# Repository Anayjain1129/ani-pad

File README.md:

# Ani-Pad

### Why did I make it?
As I already made hackpad So i wanna make sure that this submission is not hackpad
This is a easier project for highway. So, i made this project cause I use a 60% keeb which does not have a numpad and I really needed that so i asked alex can i make one and got a yes so here we go

### What was the hardest part about this ?
I had tons of issues with making the Firmware, I was really fucked up on Firmware part but I made through.

Features:

- EC11 Rotary Encoder - For Volume, Brightness etc
- 17x keys
- XIAO rp2040
- Traditional Numpad Layout
- QMK firmware
  
### Schematic

### PCB 

### Case
- Bottom

-Middle plate

- Top

### 3D view of all parts together 
-PCB

-CAD

#Yoututb Link
https://youtube.com/shorts/V-X0GS2zixY?si=X8VkAyLvjKdzDLy9

### BOM
| Name                                                          | Qty | Final Price - INR (USD) | Link                                                                                                                        |
| ------------------------------------------------------------- | --- | ----------------------- | ----------------------------------------------------------------------------------------------------------                  |
| Gateron EF Grayish                                            | 20  | 390 ($4.55)             | [here](https://neomacro.in/products/gateron-ef-grayish)                                                                     |
| Genuine Cherry MX Plate Mount Stabilizers 2U                  | 3   | 400 {$4.67}             | [here](https://stackskb.com/store/genuine-cherry-mx-plate-mount-stabilizers-2u/)                                            |
| KeyKobo Jindo Keycap Set                                      | 1   | 1,700 ($19.84)          | [here](https://neomacro.in/products/key-kobo-jindo-keycap-set?_pos=3&_sid=b1e2b9343&_ss=r&variant=48328446116118)           |
| Diode 1N4148 Through - Hole                                   | 100 | 169 ($1.97)             | [here](https://amzn.in/d/j3eLvoh)                                                                                           |
| EC11 Rotary Encoder                                           | 2   | 178 ($2.08)             | [here](https://amzn.in/d/hVRxzij)                                                                                           |
| M3 x 20mm Bolt                                                | 15  | 149 ($1.73)             | [here](https://amzn.in/d/8GRQWAB)                                                                                           |
| M3 Nuts                                                       | 8   | 100 ($1.16)             | [here](https://amzn.in/d/7UQtsm8)                                                                                           |
| M3 x 5mm Heatset Insert                                       | 25  | 179 ($2.09)             | [here](https://amzn.in/d/ixybuAc)                                                                                           |
| PCB                                                           | 5   | 2,282 ($26.63)          | 
| XIAO 2040                                                     | 1   | 1,340 ($15.64)          | [here](https://www.amazon.in/Microcontroller-Dual-Core-MicroPython-CircuitPython-Interfaces/dp/B09NNVNW7M/ref=sr_1_2_mod_primary_new?sbo=RZvfv%2F%2FHxDF%2BO5021pAnSA%3D%3D&sr=8-2)|
| Top Case                                                      | 1   | Print Legion            |
| Bottom Case                                                   | 1   | Print Legion            |
| Middle Plate                                                  | 1   | Print Legion            |

## Total Pricing 

This Numpad comes out to be 6887 INR ($80.36) When ordering all the parts I'm not including  the 3D parts because I will be getting them from Print Legion.

## Notes :-

I want all the three 3D-printed parts to be printed in black color.
The pricing might slightly vary due to flash sales, and dollar market trends.

## Changes for reboot 
https://drive.google.com/file/d/1S1DNsVMGy2zWwLPmCcZhrC4ZR8giEo4_/view?usp=sharing

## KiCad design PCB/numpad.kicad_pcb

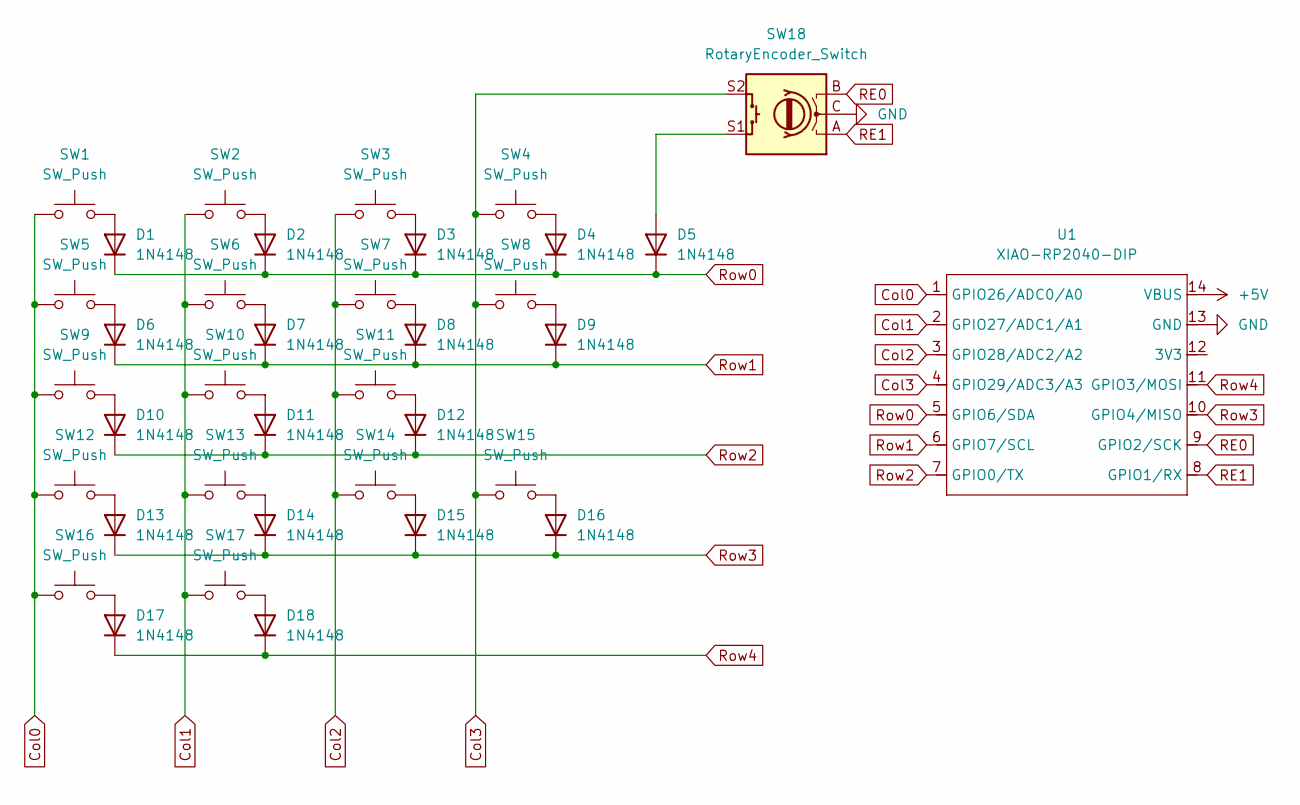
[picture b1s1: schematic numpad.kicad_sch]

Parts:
D1, D2, D3, D4, D5, D6, D7, D8, D9, D10, D11, D12, D13, D14, D15, D16, D17, D18: 1N4148; D_DO-35_SOD27_P7.62mm_Horizontal
SW1, SW2, SW3, SW4, SW5, SW6, SW7, SW9, SW10, SW11, SW12, SW13, SW14, SW17: SW_Push; SW_Cherry_MX_1.00u_PCB
SW8, SW15: SW_Push; SW_Cherry_MX_2.00u_Vertical_PCB
SW16: SW_Push; SW_Cherry_MX_2.00u_PCB
SW18: RotaryEncoder_Switch; RotaryEncoder_Alps_EC11E-Switch_Vertical_H20mm_CircularMoun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
U1: XIAO-RP2040-DIP

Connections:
+5V: U1.14 (VBUS)
Col0: SW1.1, SW5.1, SW9.1, SW12.1, SW16.1, U1.1 (GPIO26/ADC0/A0)
Col1: SW2.1, SW6.1, SW10.1, SW13.1, SW17.1, U1.2 (GPIO27/ADC1/A1)
Col2: SW3.1, SW7.1, SW11.1, SW14.1, U1.3 (GPIO28/ADC2/A2)
Col3: SW4.1, SW8.1, SW15.1, SW18.S2, U1.4 (GPIO29/ADC3/A3)
GND: SW18.C, U1.13 (GND)
unnamed: D1.2 (A), SW1.2
unnamed: D2.2 (A), SW2.2
unnamed: D3.2 (A), SW3.2
unnamed: D4.2 (A), SW4.2
unnamed: D5.2 (A), SW18.S1
unnamed: D6.2 (A), SW5.2
unnamed: D7.2 (A), SW6.2
unnamed: D8.2 (A), SW7.2
unnamed: D9.2 (A), SW8.2
unnamed: D10.2 (A), SW9.2
unnamed: D11.2 (A), SW10.2
unnamed: D12.2 (A), SW11.2
unnamed: D13.2 (A), SW12.2
unnamed: D14.2 (A), SW13.2
unnamed: D15.2 (A), SW14.2
unnamed: D16.2 (A), SW15.2
unnamed: D17.2 (A), SW16.2
unnamed: D18.2 (A), SW17.2
RE0: SW18.B, U1.9 (GPIO2/SCK)
RE1: SW18.A, U1.8 (GPIO1/RX)
Row0: D1.1 (K), D2.1 (K), D3.1 (K), D4.1 (K), D5.1 (K), U1.5 (GPIO6/SDA)
Row1: D6.1 (K), D7.1 (K), D8.1 (K), D9.1 (K), U1.6 (GPIO7/SCL)
Row2: D10.1 (K), D11.1 (K), D12.1 (K), U1.7 (GPIO0/TX)
Row3: D13.1 (K), D14.1 (K), D15.1 (K), D16.1 (K), U1.10 (GPIO4/MISO)
Row4: D17.1 (K), D18.1 (K), U1.11 (GPIO3/MOSI)

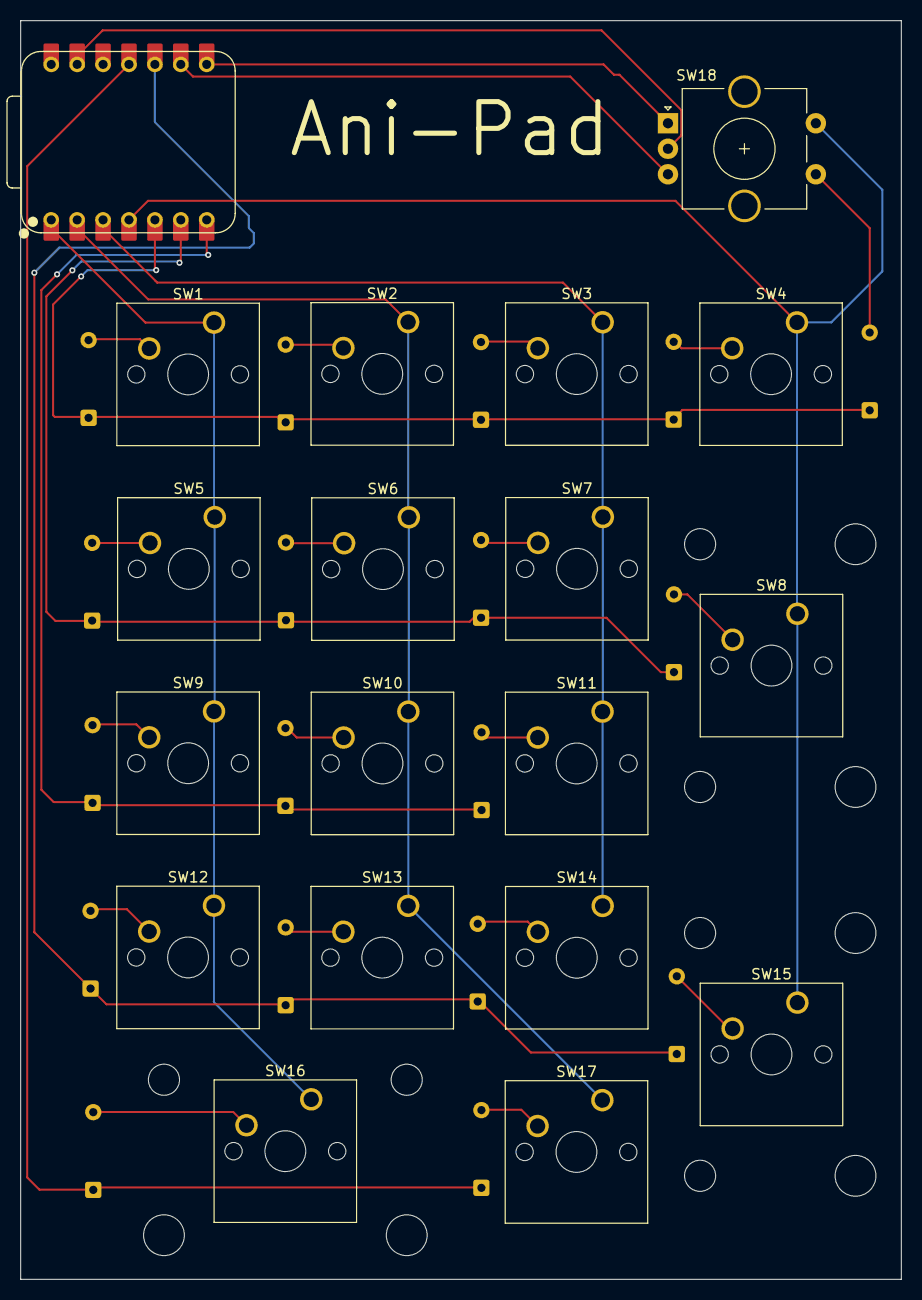
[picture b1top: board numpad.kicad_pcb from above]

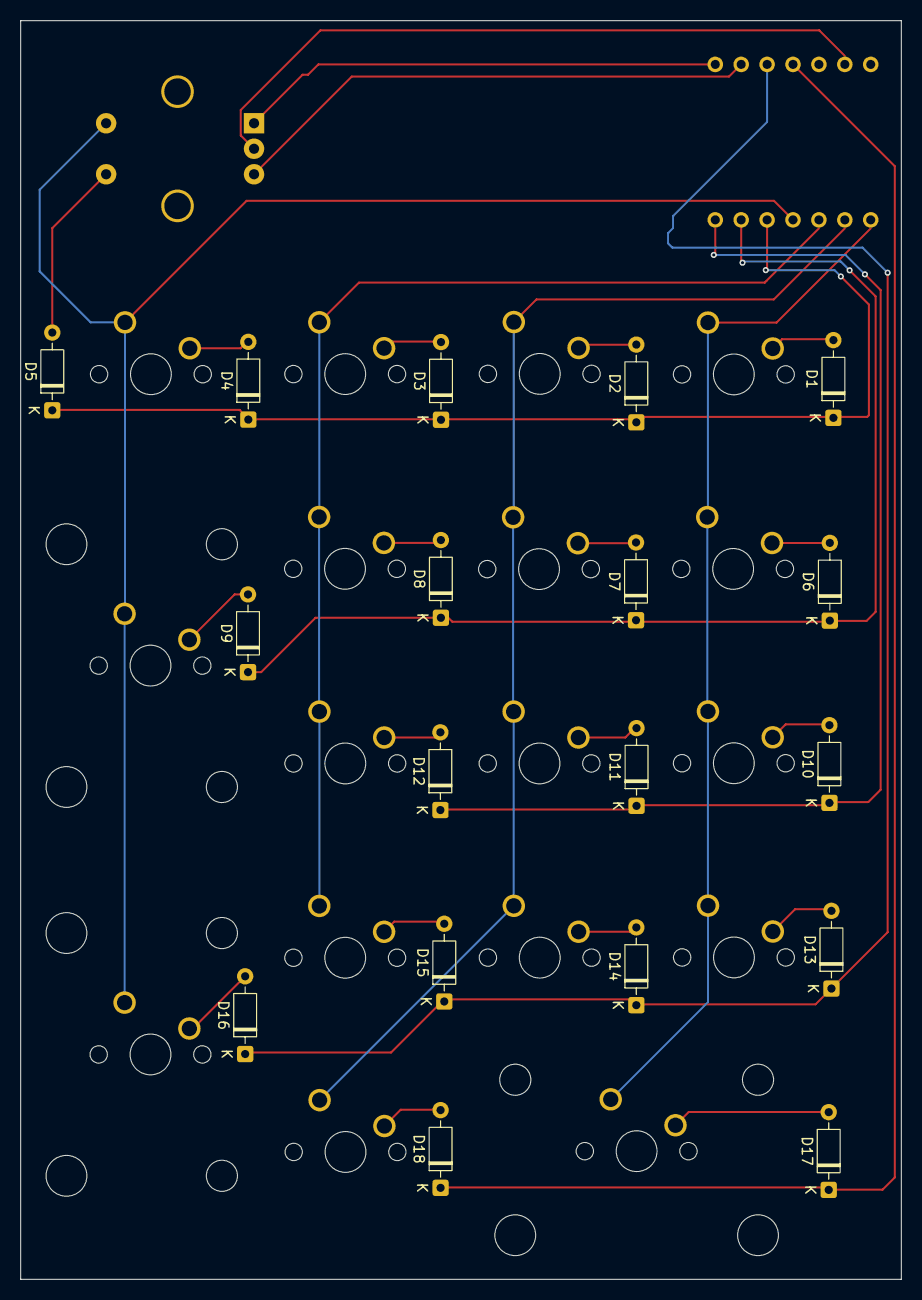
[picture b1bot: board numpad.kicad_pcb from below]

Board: 2 copper layers, 86.3 x 123.4 mm, 37 parts (18 on the bottom side), 30 nets.

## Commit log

2025-07-08 Create nill
2025-07-15 Rename Bom.csv to bom.csv
